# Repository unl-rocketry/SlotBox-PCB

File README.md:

# SlotBox PCB Files and Documentation

## Merging and Branches
Since this is confusing, here are some tips for that.

## To update a branch
```
git checkout main
git pull main
git checkout <desired branch>
git merge main
git push
```

## To merge from a branch into main
```
git checkout <desired branch>
git pull
git checkout main
git merge <desired branch>
git push
```

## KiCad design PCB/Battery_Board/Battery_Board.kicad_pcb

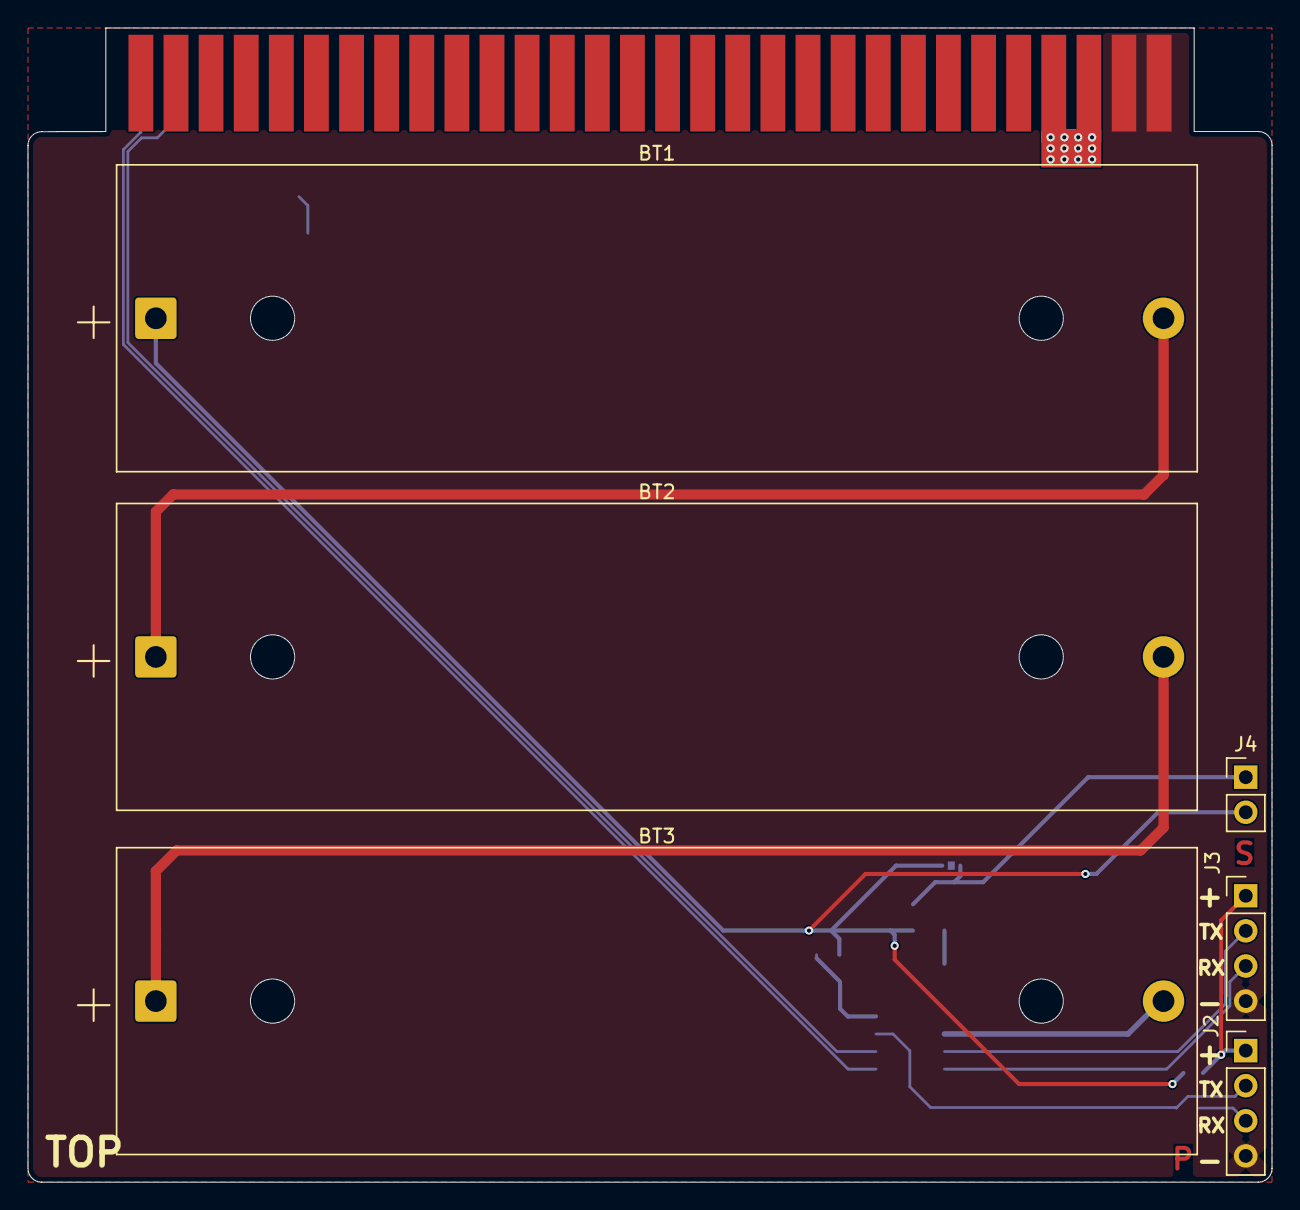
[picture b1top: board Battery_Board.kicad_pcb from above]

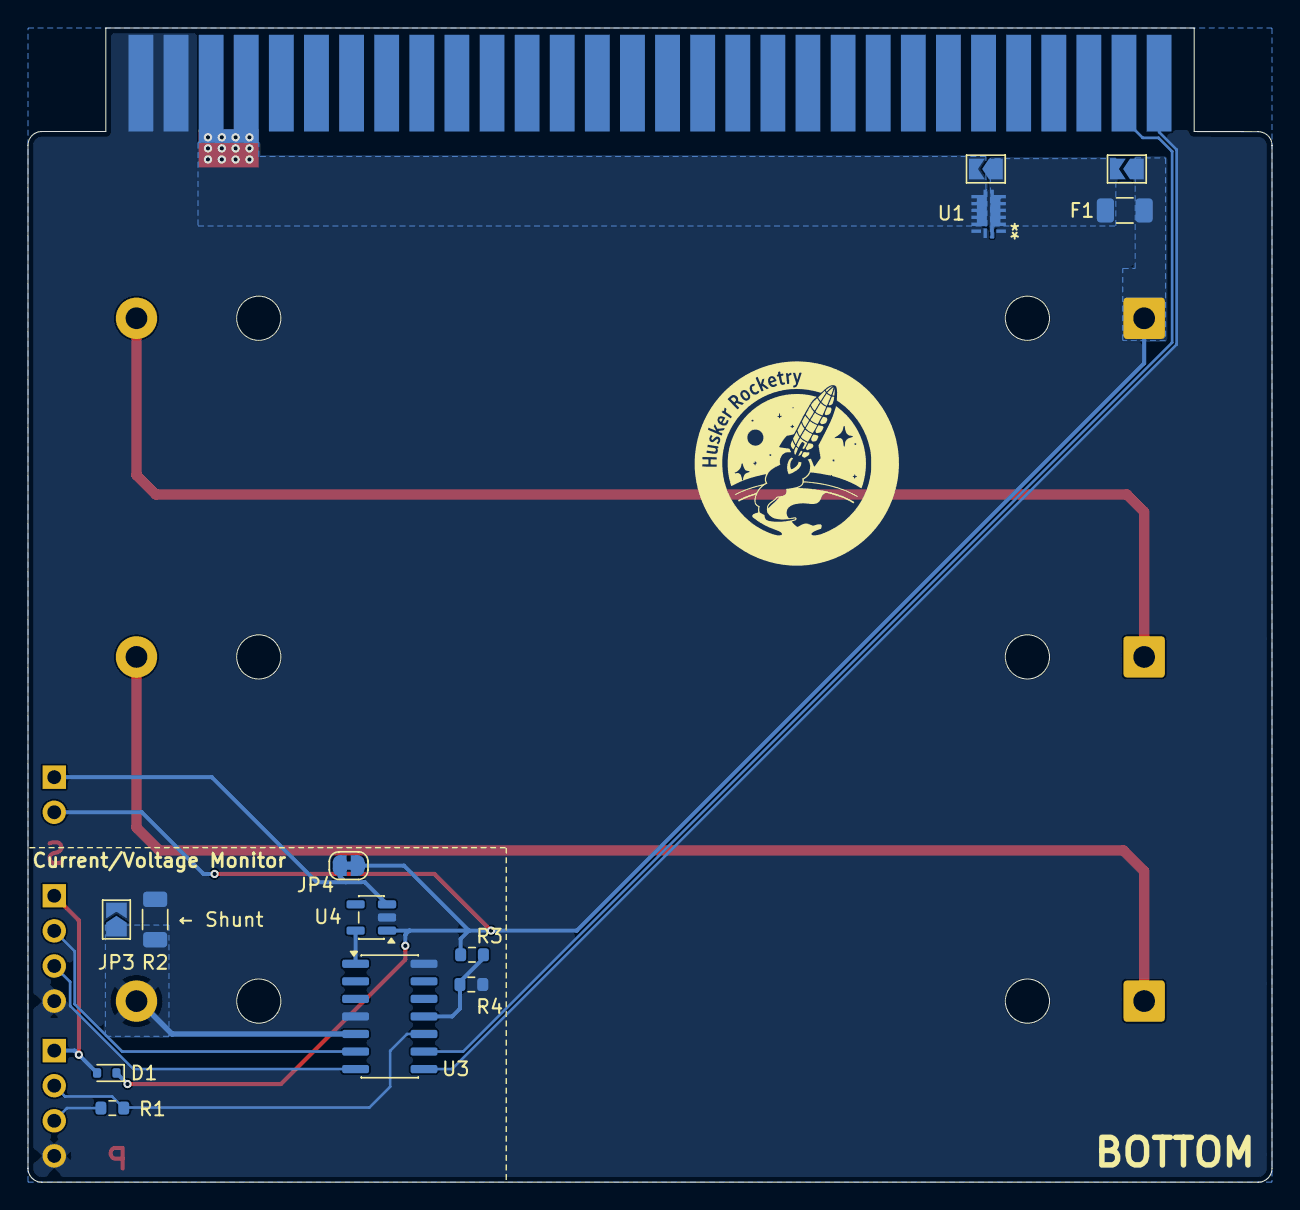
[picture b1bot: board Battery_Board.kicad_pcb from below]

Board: 2 copper layers, 90.0 x 83.5 mm, 20 parts (13 on the bottom side), 17 nets.

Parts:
BT1, BT2, BT3: Battery_Cell; BatteryHolder_MPD_BK-18650-PC2
D1: BAT54WX-TP; D_SOD-523
F1: Fuse_Small; Fuse_1206_3216Metric
J1: SE2-30
J2: UDPI; PinHeader_1x04_P2.54mm_Vertical
J3: UART0; PinHeader_1x04_P2.54mm_Vertical
J4: MCU En/Disable; PinHeader_1x02_P2.54mm_Vertical
JP1: Fuse Bypass; SolderJumper-2_P1.3mm_Open_TrianglePad1.0x1.5mm
JP2: Ideal Diode Bypass; SolderJumper-2_P1.3mm_Open_TrianglePad1.0x1.5mm
JP3: Shunt Resistor Bypass; SolderJumper-2_P1.3mm_Open_TrianglePad1.0x1.5mm
JP4: MCU Disable; SolderJumper-2_P1.3mm_Bridged_RoundedPad1.0x1.5mm
R1: 1k; R_0603_1608Metric
R2: 0.02; R_1206_3216Metric
R3: 3.3k; R_0603_1608Metric
R4: 680; R_0603_1608Metric
U1: LTC4451AV-TRPBF; 05-08-1683_ADI
U3: ATtiny1624-SS; SOIC-14_3.9x8.7mm_P1.27mm
U4: MIC5205-3.3YM5; SOT-23-5

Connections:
+3.3V: U3.1 (VCC), U4.5 (OUT)
+BATT: BT1.1 (+), D1.1 (K), F1.2, J4.2, JP1.1 (A), JP4.1 (A), R3.1, U4.1 (IN)
/DIVIDER+: R3.2, R4.1, U3.11 (PA1)
/IN_PGM_RX: J2.2, R1.2, U3.10 (~RESET/PA0)
/IN_PGM_TX: J2.3, R1.1
/MCU_PWR_EN: J4.1, JP4.2 (B), U4.3 (EN)
/MCU_RX: J3.2, U3.6 (PB3)
/MCU_SCL: J1.32 (GPIO_3), U3.9 (PB0)
/MCU_SDA: J1.31 (GPIO_2), U3.8 (PB1)
/MCU_TX: J3.3, U3.7 (PB2)
/SHUNT+: BT3.2 (-), JP3.1 (A), R2.2, U3.5 (PA7)
/USB_PWR: D1.2 (A), J2.1, J3.1
GND: J1.29 (GND), J1.30 (GND), J1.59 (GND), J1.60 (GND), J2.4, J3.4, JP3.2 (B), R2.1, R4.2, U1.1 (VCC), U1.14 (GND), U1.15 (STATUS), U3.4 (PA6), U3.14 (GND), U4.2 (GND)
unnamed: BT1.2 (-), BT2.1 (+)
unnamed: BT2.2 (-), BT3.1 (+)
unnamed: F1.1, JP1.2 (B), JP2.1 (A), U1.2 (IN), U1.3 (IN), U1.4 (IN), U1.5 (IN), U1.6 (IN), U1.7 (IN), U1.16 (SHDN#)
VBUS: J1.27 (VBus), J1.28 (VBus), J1.57 (VBus), J1.58 (VBus), JP2.2 (B), U1.8 (OUT), U1.9 (OUT), U1.10 (OUT), U1.11 (OUT), U1.12 (OUT), U1.13 (OUT)

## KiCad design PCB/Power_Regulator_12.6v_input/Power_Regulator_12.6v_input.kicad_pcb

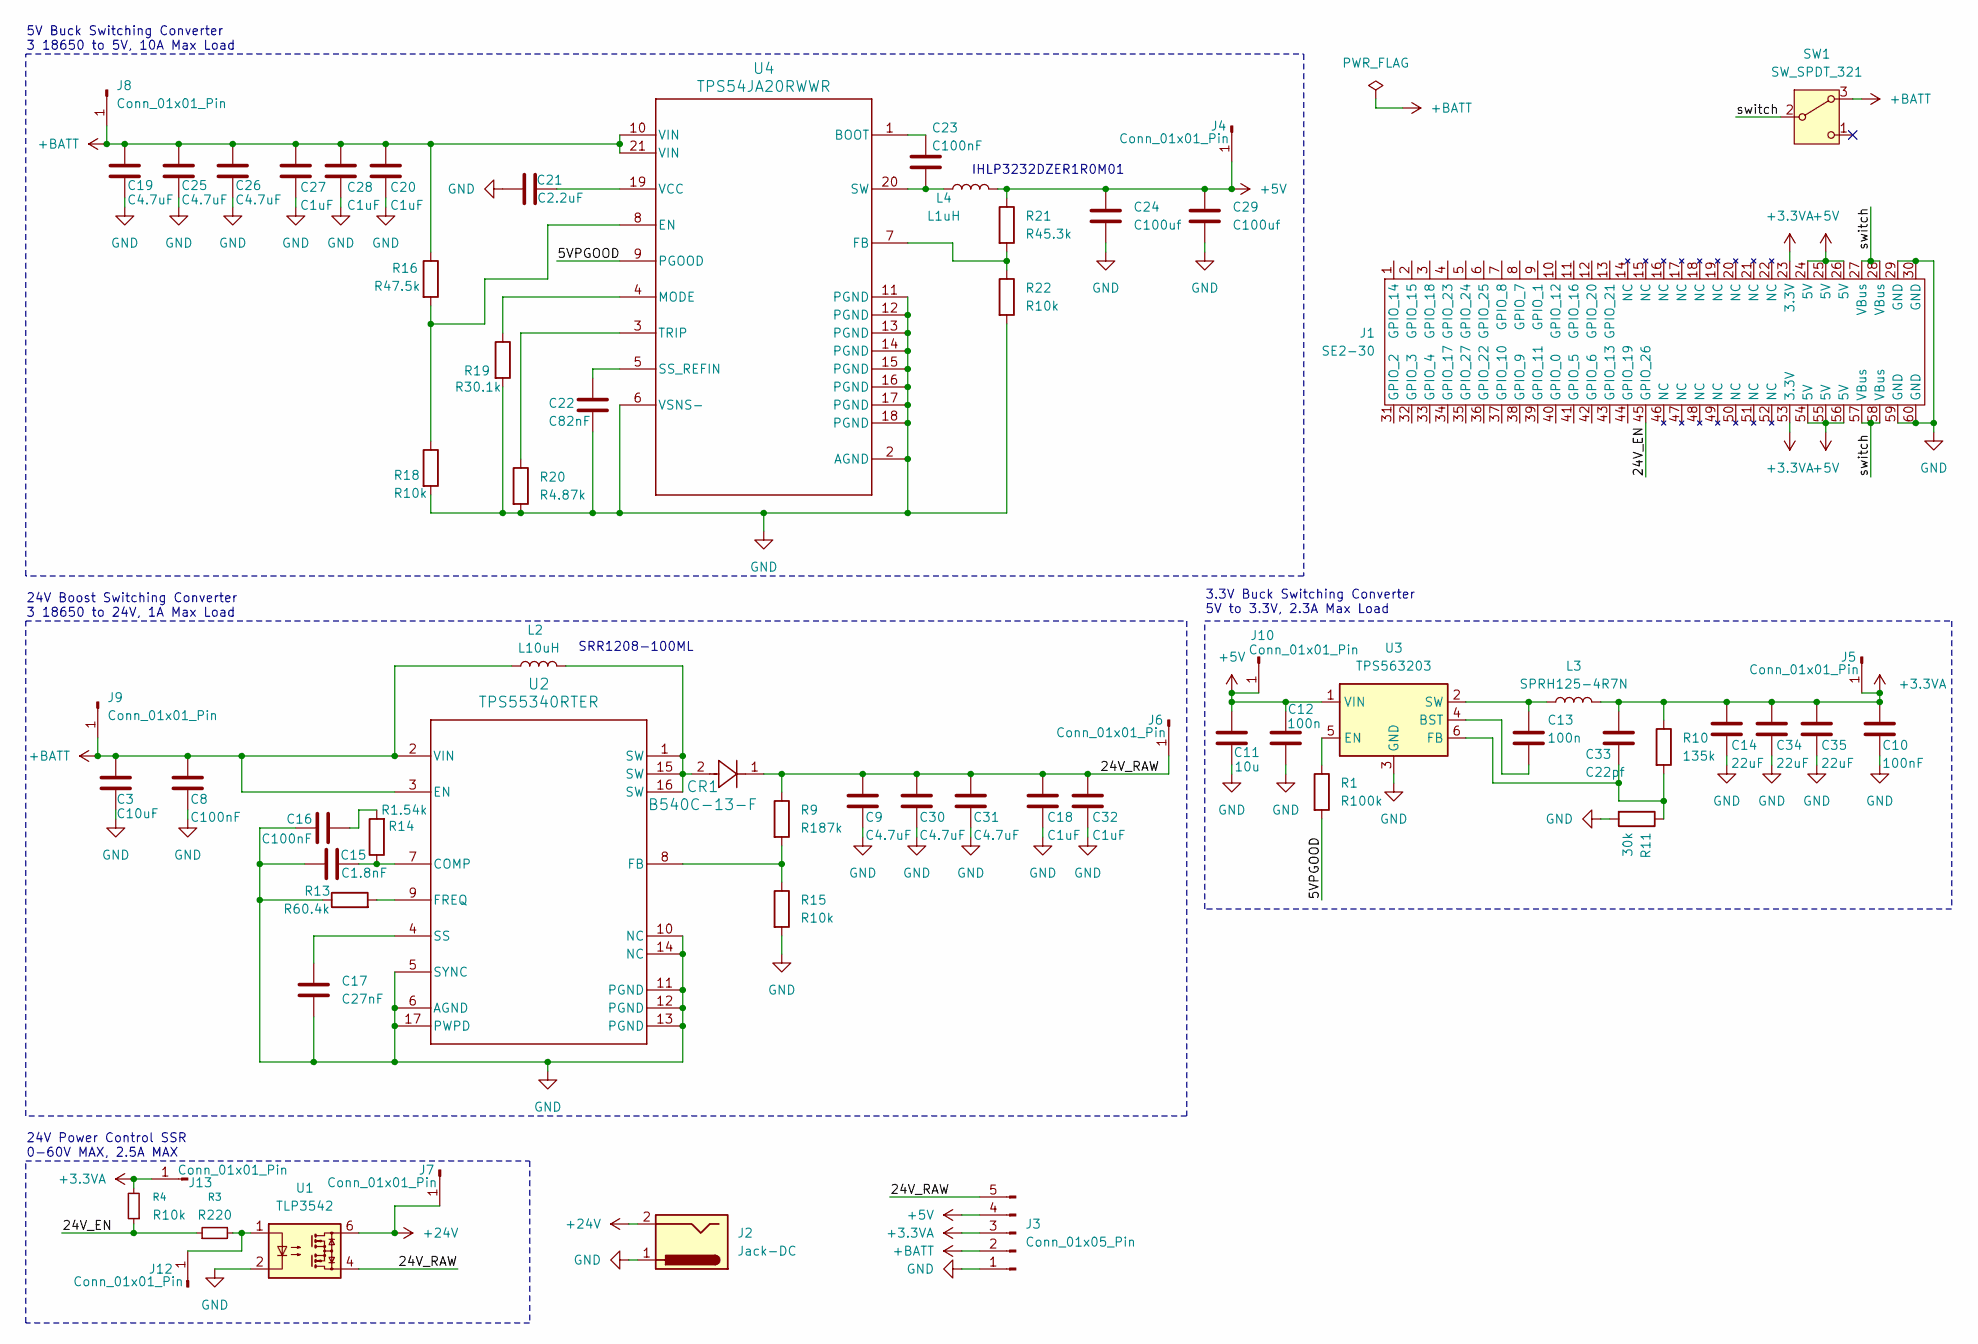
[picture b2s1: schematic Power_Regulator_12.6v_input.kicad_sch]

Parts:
C3: C10uF; C_0603_1608Metric
C8, C16, C23: C100nF; C_0603_1608Metric
C9, C19, C25, C26, C30, C31: C4.7uF; C_0603_1608Metric
C10: 100nF; C_0603_1608Metric
C11: 10u; C_0603_1608Metric
C12, C13: 100n; C_0603_1608Metric
C14, C34, C35: 22uF; C_0603_1608Metric
C15: C1.8nF; C_0603_1608Metric
C17: C27nF; C_0603_1608Metric
C18, C20, C27, C28, C32: C1uF; C_0603_1608Metric
C21: C2.2uF; C_0603_1608Metric
C22: C82nF; C_0603_1608Metric
C24, C29: C100uf; C_1206_3216Metric
C33: C22pf; C_0603_1608Metric
CR1: B540C-13-F; SMC_DIO
J1: SE2-30
J2: Jack-DC; AMASS_XT60-M_1x02_P7.20mm_Vertical
J3: Conn_01x05_Pin; PinHeader_1x05_P2.54mm_Vertical
J4, J5, J6, J7, J8, J9, J10, J12, J13: Conn_01x01_Pin; TestPoint_Pad_D1.0mm
L2: L10uH; IND_BOURNS_SRR1208
L3: SPRH125-4R7N; L_12x12mm_H6mm
L4: L1uH; IND_IHLP-3232DZ_VIS-L
R1: R100k; R_0603_1608Metric
R3: R220; R_0603_1608Metric
R4, R15, R18, R22: R10k; R_0603_1608Metric
R9: R187k; R_0603_1608Metric
R10: 135k; R_0603_1608Metric
R11: 30k; R_0603_1608Metric
R13: R60.4k; R_0603_1608Metric
R14: R1.54k; R_0603_1608Metric
R16: R47.5k; R_0603_1608Metric
R19: R30.1k; R_0603_1608Metric
R20: R4.87k; R_0603_1608Metric
R21: R45.3k; R_0603_1608Metric
SW1: SW_SPDT_321; SS-5
U1: TLP3542; DIP-5-6_W7.62mm
U2: TPS55340RTER; RTE0016C_NV
U3: TPS563203; SOT-563
U4: TPS54JA20RWWR; RWW0021A

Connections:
+3.3VA: C10.1, C14.1, C33.1, C34.1, C35.1, J1.23 (3.3V), J1.53 (3.3V), J3.3, J5.1, J13.1, L3.2, R4.2, R10.1
+5V: C11.1, C12.1, C24.1, C29.1, J1.24 (5V), J1.25 (5V), J1.26 (5V), J1.54 (5V), J1.55 (5V), J1.56 (5V), J3.4, J4.1, J10.1, L4.2, R21.1, U3.1 (VIN)
+24V: J2.2, J7.1, U1.6
+BATT: C3.1, C8.1, C19.1, C20.1, C25.1, C26.1, C27.1, C28.1, J3.2, J8.1, J9.1, L2.1, R16.1, SW1.3 (A), U2.2 (VIN), U2.3 (EN), U4.10 (VIN), U4.21 (VIN)
/5VPGOOD: R1.2, U4.9 (PGOOD)
/24V_EN: J1.45 (GPIO_26), R3.1, R4.1
/24V_RAW: C9.1, C18.1, C30.1, C31.1, C32.1, CR1.1, J3.5, J6.1, R9.1, U1.4
/switch: J1.27 (VBus), J1.28 (VBus), J1.57 (VBus), J1.58 (VBus), SW1.2 (B)
GND: C3.2, C8.2, C9.2, C10.2, C11.2, C12.2, C14.2, C15.1, C16.1, C17.1, C18.2, C19.2, C20.2, C21.1, C22.2, C24.2, C25.2, C26.2, C27.2, C28.2, C29.2, C30.2, C31.2, C32.2, C34.2, C35.2, J1.29 (GND), J1.30 (GND), J1.59 (GND), J1.60 (GND), J2.1, J3.1, R11.2, R13.1, R15.2, R18.2, R19.2, R20.2, R22.2, U1.2, U2.5 (SYNC), U2.6 (AGND), U2.10 (NC), U2.11 (PGND), U2.12 (PGND), U2.13 (PGND), U2.14 (NC), U2.17 (PWPD), U3.3 (GND), U4.2 (AGND), U4.6 (VSNS-), U4.11 (PGND), U4.12 (PGND), U4.13 (PGND), U4.14 (PGND), U4.15 (PGND), U4.16 (PGND), U4.17 (PGND), U4.18 (PGND)
unnamed: C16.2, R14.2
unnamed: CR1.2, L2.2, U2.1 (SW), U2.15 (SW), U2.16 (SW)
unnamed: J12.1, R3.2, U1.1
unnamed: C15.2, R14.1, U2.7 (COMP)
unnamed: R9.2, R15.1, U2.8 (FB)
unnamed: R13.2, U2.9 (FREQ)
unnamed: C17.2, U2.4 (SS)
unnamed: C13.2, U3.4 (BST)
unnamed: R1.1, U3.5 (EN)
unnamed: C33.2, R10.2, R11.1, U3.6 (FB)
unnamed: C13.1, L3.1, U3.2 (SW)
unnamed: C23.2, U4.1 (BOOT)
unnamed: R16.2, R18.1, U4.8 (EN)
unnamed: R21.2, R22.1, U4.7 (FB)
unnamed: R19.1, U4.4 (MODE)
unnamed: C22.1, U4.5 (SS_REFIN)
unnamed: C23.1, L4.1, U4.20 (SW)
unnamed: R20.1, U4.3 (TRIP)
unnamed: C21.2, U4.19 (VCC)

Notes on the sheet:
3.3V Buck Switching Converter 5V to 3.3V, 2.3A Max Load
IHLP3232DZER1R0M01
5V Buck Switching Converter 3 18650 to 5V, 10A Max Load
24V Power Control SSR 0-60V MAX, 2.5A MAX
24V Boost Switching Converter 3 18650 to 24V, 1A Max Load
SRR1208-100ML

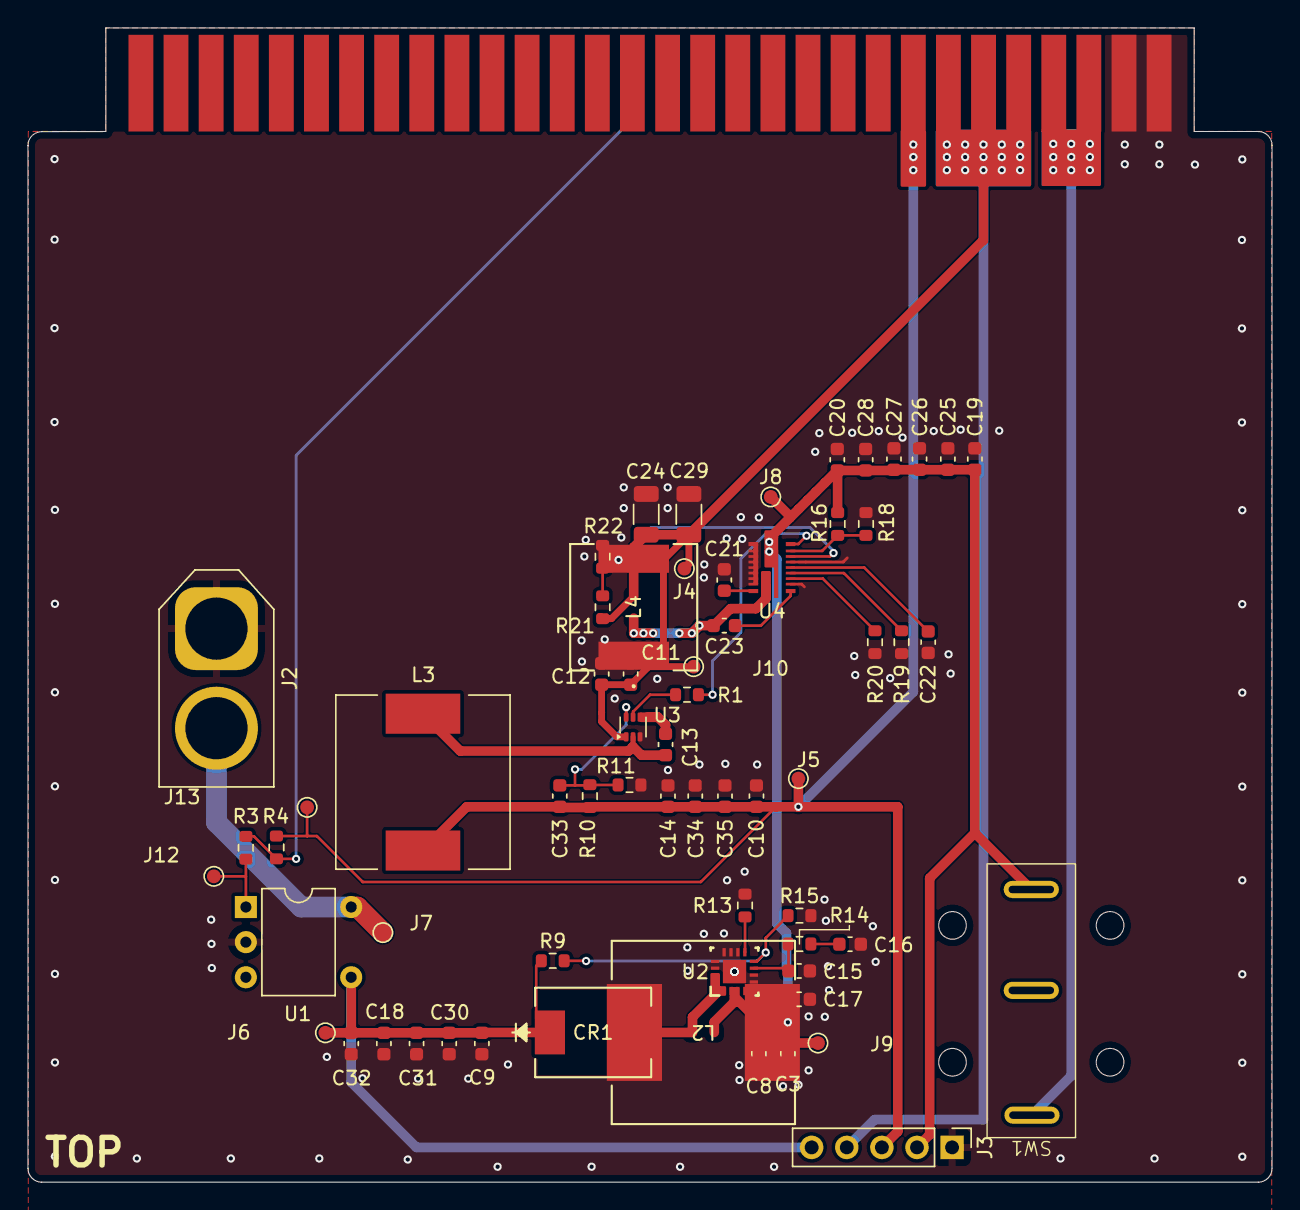
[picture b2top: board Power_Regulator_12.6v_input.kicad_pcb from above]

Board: 2 copper layers, 90.0 x 83.5 mm, 65 parts (0 on the bottom side), 28 nets.

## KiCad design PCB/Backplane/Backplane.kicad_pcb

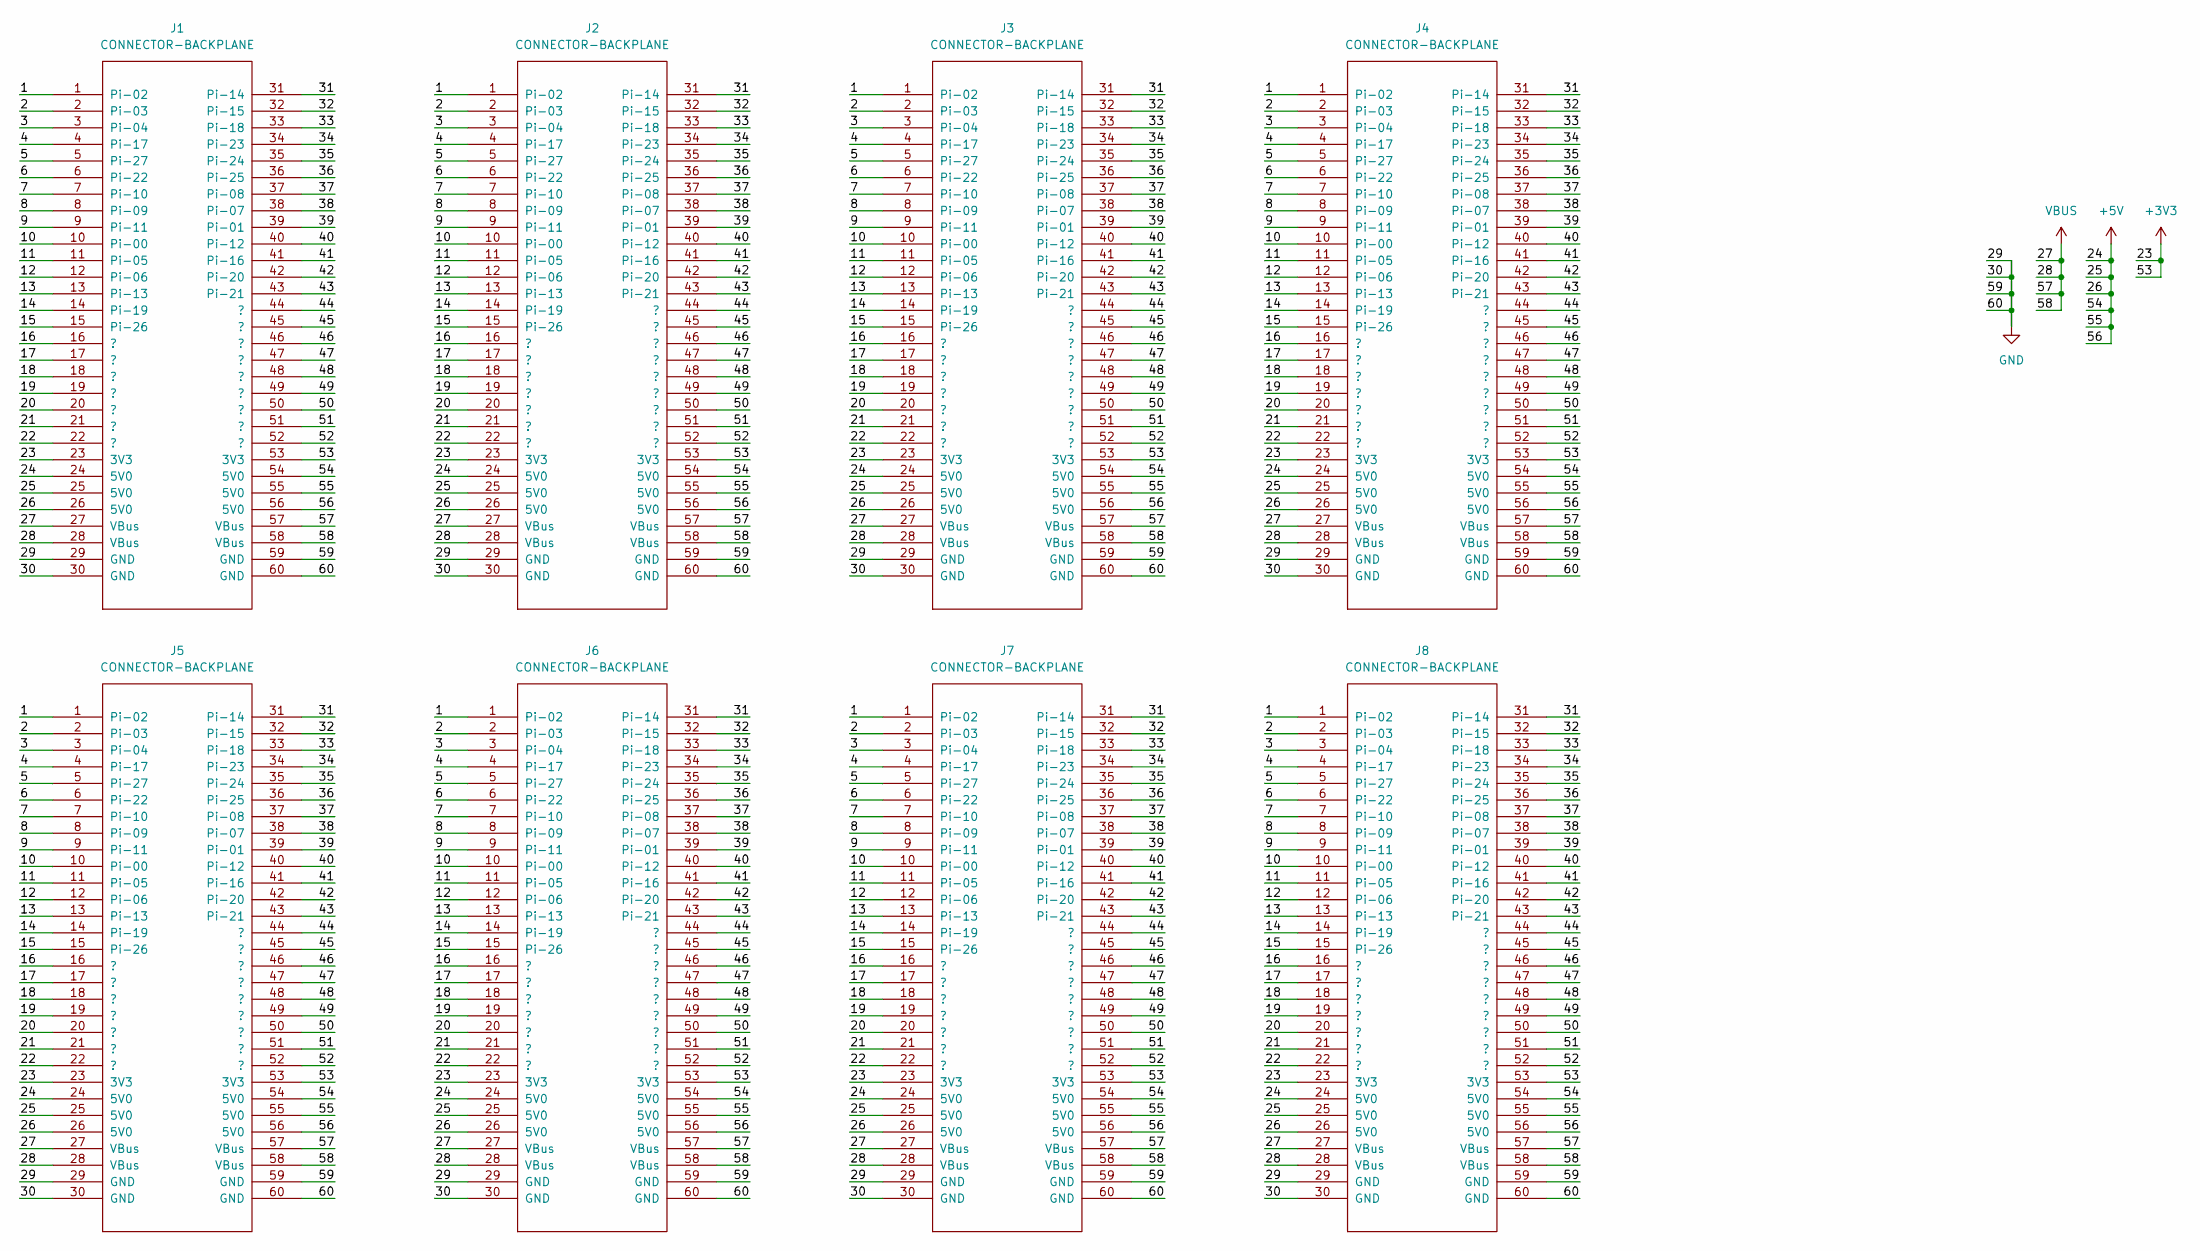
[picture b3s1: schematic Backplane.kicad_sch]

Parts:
J1, J2, J3, J4, J5, J6, J7, J8: CONNECTOR-BACKPLANE; TE_5530843-7

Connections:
+3V3: J1.23 (3V3), J1.53 (3V3), J2.23 (3V3), J2.53 (3V3), J3.23 (3V3), J3.53 (3V3), J4.23 (3V3), J4.53 (3V3), J5.23 (3V3), J5.53 (3V3), J6.23 (3V3), J6.53 (3V3), J7.23 (3V3), J7.53 (3V3), J8.23 (3V3), J8.53 (3V3)
+5V: J1.24 (5V0), J1.25 (5V0), J1.26 (5V0), J1.54 (5V0), J1.55 (5V0), J1.56 (5V0), J2.24 (5V0), J2.25 (5V0), J2.26 (5V0), J2.54 (5V0), J2.55 (5V0), J2.56 (5V0), J3.24 (5V0), J3.25 (5V0), J3.26 (5V0), J3.54 (5V0), J3.55 (5V0), J3.56 (5V0), J4.24 (5V0), J4.25 (5V0), J4.26 (5V0), J4.54 (5V0), J4.55 (5V0), J4.56 (5V0), J5.24 (5V0), J5.25 (5V0), J5.26 (5V0), J5.54 (5V0), J5.55 (5V0), J5.56 (5V0), J6.24 (5V0), J6.25 (5V0), J6.26 (5V0), J6.54 (5V0), J6.55 (5V0), J6.56 (5V0), J7.24 (5V0), J7.25 (5V0), J7.26 (5V0), J7.54 (5V0), J7.55 (5V0), J7.56 (5V0), J8.24 (5V0), J8.25 (5V0), J8.26 (5V0), J8.54 (5V0), J8.55 (5V0), J8.56 (5V0)
/1: J1.1 (Pi-02), J2.1 (Pi-02), J3.1 (Pi-02), J4.1 (Pi-02), J5.1 (Pi-02), J6.1 (Pi-02), J7.1 (Pi-02), J8.1 (Pi-02)
/2: J1.2 (Pi-03), J2.2 (Pi-03), J3.2 (Pi-03), J4.2 (Pi-03), J5.2 (Pi-03), J6.2 (Pi-03), J7.2 (Pi-03), J8.2 (Pi-03)
/3: J1.3 (Pi-04), J2.3 (Pi-04), J3.3 (Pi-04), J4.3 (Pi-04), J5.3 (Pi-04), J6.3 (Pi-04), J7.3 (Pi-04), J8.3 (Pi-04)
/4: J1.4 (Pi-17), J2.4 (Pi-17), J3.4 (Pi-17), J4.4 (Pi-17), J5.4 (Pi-17), J6.4 (Pi-17), J7.4 (Pi-17), J8.4 (Pi-17)
/5: J1.5 (Pi-27), J2.5 (Pi-27), J3.5 (Pi-27), J4.5 (Pi-27), J5.5 (Pi-27), J6.5 (Pi-27), J7.5 (Pi-27), J8.5 (Pi-27)
/6: J1.6 (Pi-22), J2.6 (Pi-22), J3.6 (Pi-22), J4.6 (Pi-22), J5.6 (Pi-22), J6.6 (Pi-22), J7.6 (Pi-22), J8.6 (Pi-22)
/7: J1.7 (Pi-10), J2.7 (Pi-10), J3.7 (Pi-10), J4.7 (Pi-10), J5.7 (Pi-10), J6.7 (Pi-10), J7.7 (Pi-10), J8.7 (Pi-10)
/8: J1.8 (Pi-09), J2.8 (Pi-09), J3.8 (Pi-09), J4.8 (Pi-09), J5.8 (Pi-09), J6.8 (Pi-09), J7.8 (Pi-09), J8.8 (Pi-09)
/9: J1.9 (Pi-11), J2.9 (Pi-11), J3.9 (Pi-11), J4.9 (Pi-11), J5.9 (Pi-11), J6.9 (Pi-11), J7.9 (Pi-11), J8.9 (Pi-11)
/10: J1.10 (Pi-00), J2.10 (Pi-00), J3.10 (Pi-00), J4.10 (Pi-00), J5.10 (Pi-00), J6.10 (Pi-00), J7.10 (Pi-00), J8.10 (Pi-00)
/11: J1.11 (Pi-05), J2.11 (Pi-05), J3.11 (Pi-05), J4.11 (Pi-05), J5.11 (Pi-05), J6.11 (Pi-05), J7.11 (Pi-05), J8.11 (Pi-05)
/12: J1.12 (Pi-06), J2.12 (Pi-06), J3.12 (Pi-06), J4.12 (Pi-06), J5.12 (Pi-06), J6.12 (Pi-06), J7.12 (Pi-06), J8.12 (Pi-06)
/13: J1.13 (Pi-13), J2.13 (Pi-13), J3.13 (Pi-13), J4.13 (Pi-13), J5.13 (Pi-13), J6.13 (Pi-13), J7.13 (Pi-13), J8.13 (Pi-13)
/14: J1.14 (Pi-19), J2.14 (Pi-19), J3.14 (Pi-19), J4.14 (Pi-19), J5.14 (Pi-19), J6.14 (Pi-19), J7.14 (Pi-19), J8.14 (Pi-19)
/15: J1.15 (Pi-26), J2.15 (Pi-26), J3.15 (Pi-26), J4.15 (Pi-26), J5.15 (Pi-26), J6.15 (Pi-26), J7.15 (Pi-26), J8.15 (Pi-26)
/16: J1.16 (?), J2.16 (?), J3.16 (?), J4.16 (?), J5.16 (?), J6.16 (?), J7.16 (?), J8.16 (?)
/17: J1.17 (?), J2.17 (?), J3.17 (?), J4.17 (?), J5.17 (?), J6.17 (?), J7.17 (?), J8.17 (?)
/18: J1.18 (?), J2.18 (?), J3.18 (?), J4.18 (?), J5.18 (?), J6.18 (?), J7.18 (?), J8.18 (?)
/19: J1.19 (?), J2.19 (?), J3.19 (?), J4.19 (?), J5.19 (?), J6.19 (?), J7.19 (?), J8.19 (?)
/20: J1.20 (?), J2.20 (?), J3.20 (?), J4.20 (?), J5.20 (?), J6.20 (?), J7.20 (?), J8.20 (?)
/21: J1.21 (?), J2.21 (?), J3.21 (?), J4.21 (?), J5.21 (?), J6.21 (?), J7.21 (?), J8.21 (?)
/22: J1.22 (?), J2.22 (?), J3.22 (?), J4.22 (?), J5.22 (?), J6.22 (?), J7.22 (?), J8.22 (?)
/31: J1.31 (Pi-14), J2.31 (Pi-14), J3.31 (Pi-14), J4.31 (Pi-14), J5.31 (Pi-14), J6.31 (Pi-14), J7.31 (Pi-14), J8.31 (Pi-14)
/32: J1.32 (Pi-15), J2.32 (Pi-15), J3.32 (Pi-15), J4.32 (Pi-15), J5.32 (Pi-15), J6.32 (Pi-15), J7.32 (Pi-15), J8.32 (Pi-15)
/33: J1.33 (Pi-18), J2.33 (Pi-18), J3.33 (Pi-18), J4.33 (Pi-18), J5.33 (Pi-18), J6.33 (Pi-18), J7.33 (Pi-18), J8.33 (Pi-18)
/34: J1.34 (Pi-23), J2.34 (Pi-23), J3.34 (Pi-23), J4.34 (Pi-23), J5.34 (Pi-23), J6.34 (Pi-23), J7.34 (Pi-23), J8.34 (Pi-23)
/35: J1.35 (Pi-24), J2.35 (Pi-24), J3.35 (Pi-24), J4.35 (Pi-24), J5.35 (Pi-24), J6.35 (Pi-24), J7.35 (Pi-24), J8.35 (Pi-24)
/36: J1.36 (Pi-25), J2.36 (Pi-25), J3.36 (Pi-25), J4.36 (Pi-25), J5.36 (Pi-25), J6.36 (Pi-25), J7.36 (Pi-25), J8.36 (Pi-25)
/37: J1.37 (Pi-08), J2.37 (Pi-08), J3.37 (Pi-08), J4.37 (Pi-08), J5.37 (Pi-08), J6.37 (Pi-08), J7.37 (Pi-08), J8.37 (Pi-08)
/38: J1.38 (Pi-07), J2.38 (Pi-07), J3.38 (Pi-07), J4.38 (Pi-07), J5.38 (Pi-07), J6.38 (Pi-07), J7.38 (Pi-07), J8.38 (Pi-07)
/39: J1.39 (Pi-01), J2.39 (Pi-01), J3.39 (Pi-01), J4.39 (Pi-01), J5.39 (Pi-01), J6.39 (Pi-01), J7.39 (Pi-01), J8.39 (Pi-01)
/40: J1.40 (Pi-12), J2.40 (Pi-12), J3.40 (Pi-12), J4.40 (Pi-12), J5.40 (Pi-12), J6.40 (Pi-12), J7.40 (Pi-12), J8.40 (Pi-12)
/41: J1.41 (Pi-16), J2.41 (Pi-16), J3.41 (Pi-16), J4.41 (Pi-16), J5.41 (Pi-16), J6.41 (Pi-16), J7.41 (Pi-16), J8.41 (Pi-16)
/42: J1.42 (Pi-20), J2.42 (Pi-20), J3.42 (Pi-20), J4.42 (Pi-20), J5.42 (Pi-20), J6.42 (Pi-20), J7.42 (Pi-20), J8.42 (Pi-20)
/43: J1.43 (Pi-21), J2.43 (Pi-21), J3.43 (Pi-21), J4.43 (Pi-21), J5.43 (Pi-21), J6.43 (Pi-21), J7.43 (Pi-21), J8.43 (Pi-21)
/44: J1.44 (?), J2.44 (?), J3.44 (?), J4.44 (?), J5.44 (?), J6.44 (?), J7.44 (?), J8.44 (?)
/45: J1.45 (?), J2.45 (?), J3.45 (?), J4.45 (?), J5.45 (?), J6.45 (?), J7.45 (?), J8.45 (?)
/46: J1.46 (?), J2.46 (?), J3.46 (?), J4.46 (?), J5.46 (?), J6.46 (?), J7.46 (?), J8.46 (?)
/47: J1.47 (?), J2.47 (?), J3.47 (?), J4.47 (?), J5.47 (?), J6.47 (?), J7.47 (?), J8.47 (?)
/48: J1.48 (?), J2.48 (?), J3.48 (?), J4.48 (?), J5.48 (?), J6.48 (?), J7.48 (?), J8.48 (?)
/49: J1.49 (?), J2.49 (?), J3.49 (?), J4.49 (?), J5.49 (?), J6.49 (?), J7.49 (?), J8.49 (?)
/50: J1.50 (?), J2.50 (?), J3.50 (?), J4.50 (?), J5.50 (?), J6.50 (?), J7.50 (?), J8.50 (?)
/51: J1.51 (?), J2.51 (?), J3.51 (?), J4.51 (?), J5.51 (?), J6.51 (?), J7.51 (?), J8.51 (?)
/52: J1.52 (?), J2.52 (?), J3.52 (?), J4.52 (?), J5.52 (?), J6.52 (?), J7.52 (?), J8.52 (?)
GND: J1.29 (GND), J1.30 (GND), J1.59 (GND), J1.60 (GND), J2.29 (GND), J2.30 (GND), J2.59 (GND), J2.60 (GND), J3.29 (GND), J3.30 (GND), J3.59 (GND), J3.60 (GND), J4.29 (GND), J4.30 (GND), J4.59 (GND), J4.60 (GND), J5.29 (GND), J5.30 (GND), J5.59 (GND), J5.60 (GND), J6.29 (GND), J6.30 (GND), J6.59 (GND), J6.60 (GND), J7.29 (GND), J7.30 (GND), J7.59 (GND), J7.60 (GND), J8.29 (GND), J8.30 (GND), J8.59 (GND), J8.60 (GND)
VBUS: J1.27 (VBus), J1.28 (VBus), J1.57 (VBus), J1.58 (VBus), J2.27 (VBus), J2.28 (VBus), J2.57 (VBus), J2.58 (VBus), J3.27 (VBus), J3.28 (VBus), J3.57 (VBus), J3.58 (VBus), J4.27 (VBus), J4.28 (VBus), J4.57 (VBus), J4.58 (VBus), J5.27 (VBus), J5.28 (VBus), J5.57 (VBus), J5.58 (VBus), J6.27 (VBus), J6.28 (VBus), J6.57 (VBus), J6.58 (VBus), J7.27 (VBus), J7.28 (VBus), J7.57 (VBus), J7.58 (VBus), J8.27 (VBus), J8.28 (VBus), J8.57 (VBus), J8.58 (VBus)

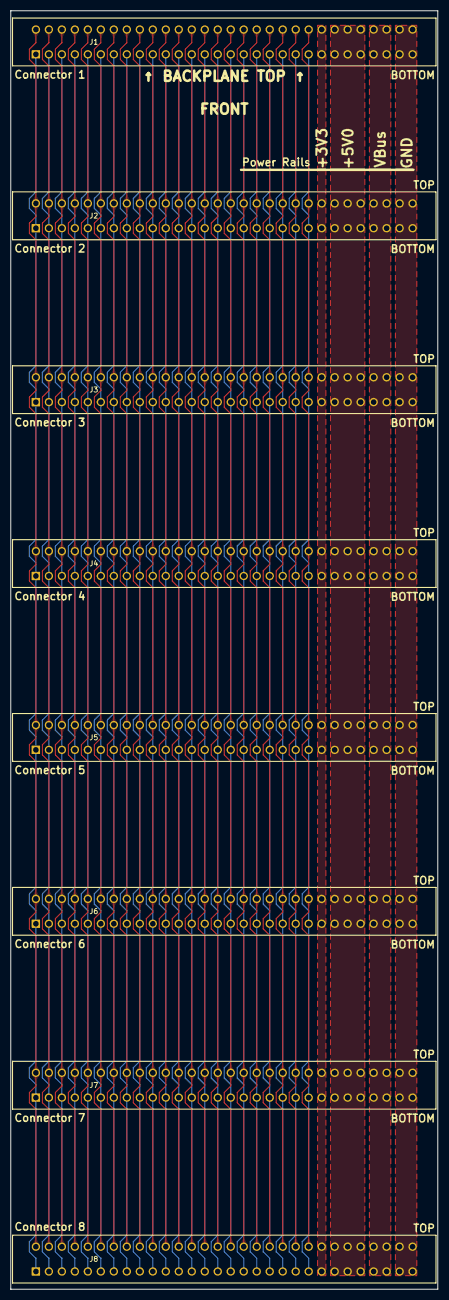
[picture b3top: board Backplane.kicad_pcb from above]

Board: 2 copper layers, 83.5 x 250.0 mm, 8 parts (0 on the bottom side), 48 nets.

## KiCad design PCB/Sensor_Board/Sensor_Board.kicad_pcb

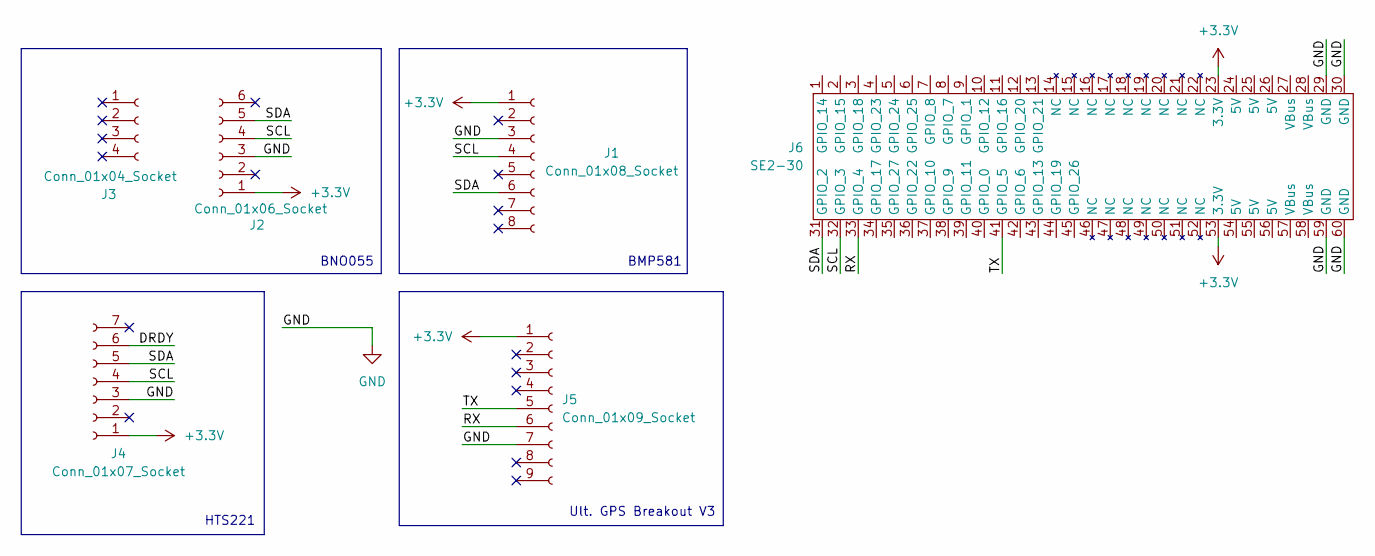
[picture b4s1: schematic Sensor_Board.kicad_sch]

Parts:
J1: Conn_01x08_Socket; PinSocket_1x08_P2.54mm_Vertical
J2: Conn_01x06_Socket; PinSocket_1x06_P2.54mm_Vertical
J3: Conn_01x04_Socket; PinSocket_1x04_P2.54mm_Vertical
J4: Conn_01x07_Socket; PinSocket_1x07_P2.54mm_Vertical
J5: Conn_01x09_Socket; PinSocket_1x09_P2.54mm_Vertical
J6: SE2-30

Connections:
+3.3V: J1.1, J2.1, J4.1, J5.1, J6.23 (3.3V), J6.53 (3.3V)
/DRDY: J4.6
/RX: J5.6, J6.33 (GPIO_4)
/SCL: J1.4, J2.4, J4.4, J6.32 (GPIO_3)
/SDA: J1.6, J2.5, J4.5, J6.31 (GPIO_2)
/TX: J5.5, J6.41 (GPIO_5)
GND: J1.3, J2.3, J4.3, J5.7, J6.29 (GND), J6.30 (GND), J6.59 (GND), J6.60 (GND)

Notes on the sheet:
BMP581
HTS221
BNO055
Ult. GPS Breakout V3

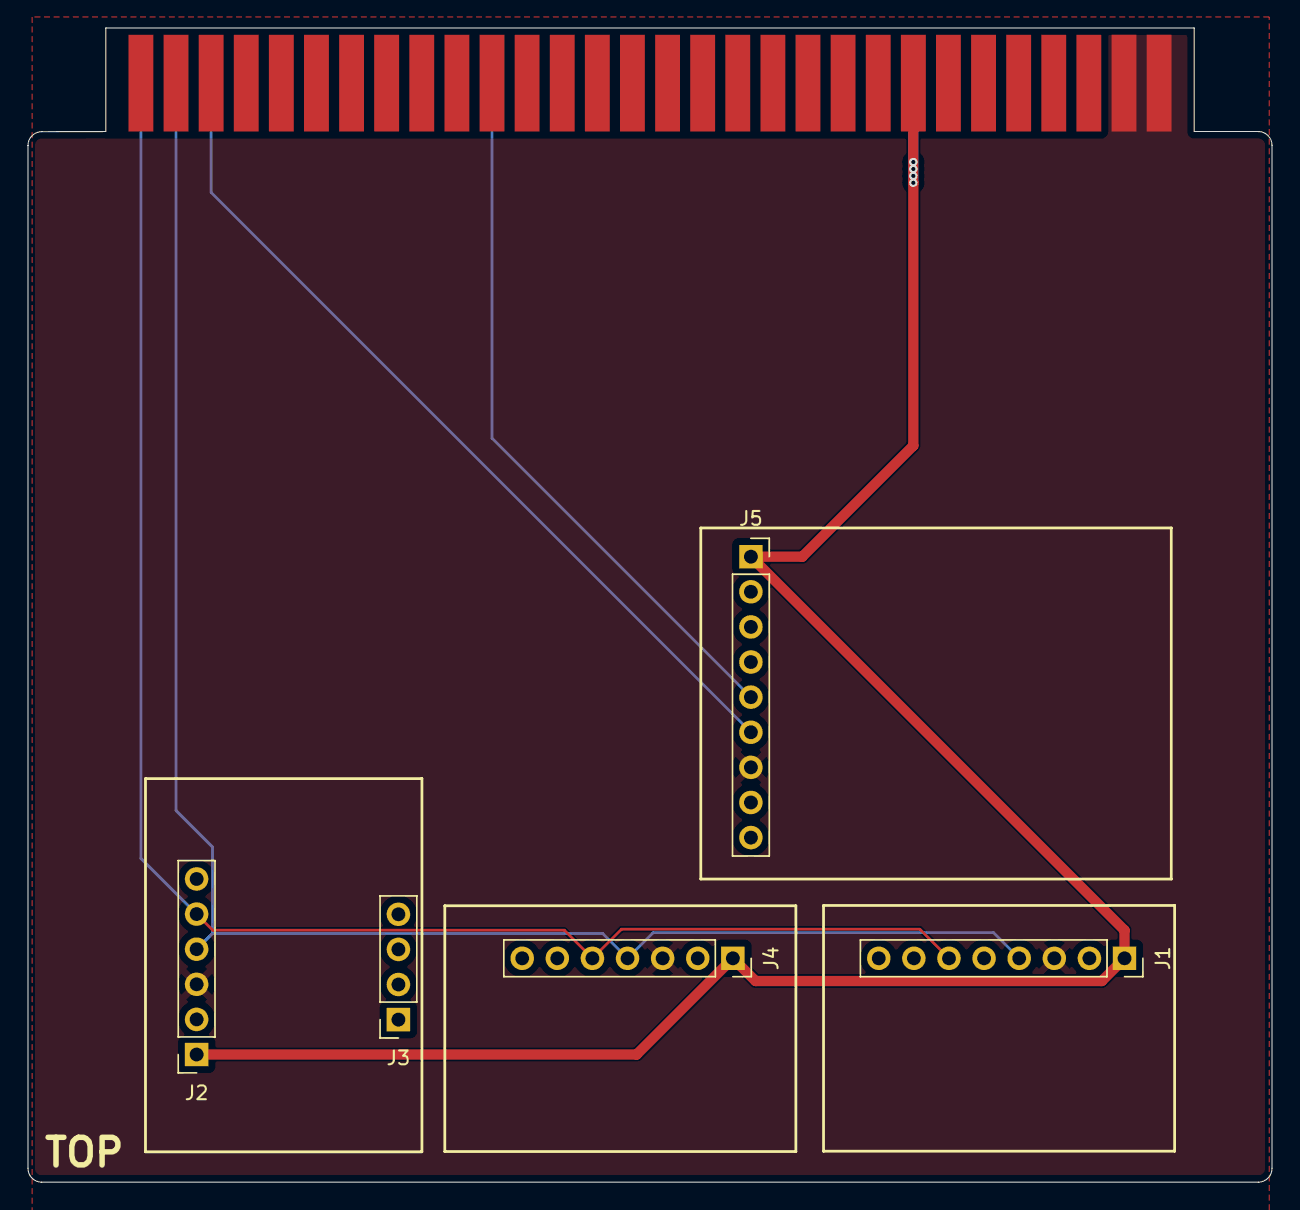
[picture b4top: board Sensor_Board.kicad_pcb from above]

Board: 2 copper layers, 90.0 x 83.5 mm, 6 parts (0 on the bottom side), 6 nets.
